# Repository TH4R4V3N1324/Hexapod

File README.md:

# Hexapod

This repository contains the complete design, control software and documentation for a six-legged walking robot (hexapod). The project combines robotics, kinematics, embedded systems, and motion planning to create a stable and adaptable walking platform.

---

## Table of Contents

- [About](#about)
- [Features](#features)
- [Installation](#installation)
  - [Hexapod](#hexapod)
  - [Receiver & Controller](#receiver--controller)
- [Usage](#usage)

---

## About

This project was developed to address the growing complexity in robotic control systems, where tightly coupled codebases often hinder scalability, debugging, and long-term maintainability. It is designed for developers, researchers, or engineers working with robotic platforms or automation systems who require a clean, extensible control framework that’s easy to understand and build upon.

The primary goal of the project was to emphasize modularity, ensuring that each component of the control software is clearly separated by function and responsibility. This modular design allows developers to quickly comprehend the structure of the system, make targeted changes without unintended side effects, and expand the system by adding new features or improving existing ones without rewriting the entire codebase.

To achieve this, the software is structured around a set of well-defined classes, each serving a distinct role:

- DataPacket Class: Acts as a container for incoming or outgoing data, ensuring that all communication between system components remains consistent, structured, and easily interpretable.

- Calculate Class: Handles all mathematical and logical computations required by the system, such as sensor data interpretation, decision-making algorithms, or movement planning.

- Move Class: Directly interfaces with the actuators or motors, translating high-level commands into specific movement instructions. It abstracts the hardware layer, allowing for easier adaptation across different platforms.

- Animation Class: Manages co-ordination of legs using the various gaits and modes to create walking and animation.

---

## Features

- 3 DOF per leg
- Inverse Kinematic engine for stable gait control
- Multiple gait patterns: tripod, ripple, wave
- Multiple control modes: normal, strafe, tilt
- Real-time control via Pimironi Servo2040
- Wireless control using custom controller and EspNOW protocol
- STL files for 3D-printing mechanical components

---

## Installation

Describe how to get your project running locally. Include prerequisites, dependencies, and step-by-step instructions.

Clone the repository into the desired location using the git bash terminal.
```bash
git clone https://github.com/TH4R4V3N1324/Hexapod.git
```

### Hexapod
Before getting started, make sure you have the following installed:

#### Prerequisites
- [Visual Studio Code](https://code.visualstudio.com/)
- [Pico SDK and cmake toolchain](https://github.com/raspberrypi/pico-sdk)
- [Raspberry Pi Pico VSCode Extension](https://marketplace.visualstudio.com/items?itemName=raspberry-pi.raspberry-pi-pico)

#### Dependencies
- [Pimironi pico sdk](https://github.com/pimoroni/pimoroni-pico.git)

Using the Raspberry Pi Pico VSCode extension, import the Hexapod sub-folder by selecting it in the **Location** tab, enabling **CMake-Tools** and clicking **Import**. 

A selection box will appear at the top of the screen. From the list, choose the appropriate Pico compiler.

Once imported, you can build the project by selecting **Compile Project** from the Pico extension commands. This will generate a .uf2 firmware file inside the build directory.

To flash the firmware to the Pimoroni Servo 2040, put the board into BOOTSEL mode (by holding the BOOT button and pressing RESET), then copy the .uf2 file to the mounted USB storage.

Alternatively, you can enter BOOTSEL mode first, then simply use the **Run Project** command. This will automatically build and flash the firmware to the board, no manual file transfer required.

### Receiver & Controller

#### Prerequisites
- [PlatformIO VSCode Extension](https://marketplace.visualstudio.com/items?itemName=platformio.platformio-ide)

#### Dependencies
- [u8g2 library](https://github.com/olikraus/u8g2.git)

Using the PlatformIO extension in VS Code, select the **Open** option under the **Quick Access** panel to launch the PlatformIO Home page. From there, click **Open Project** and navigate to the appropriate sub-folder to import your project.

To build or upload the project to your ESP32 board, use the **Build** or **Upload** options available under the **Project Tasks** panel in the PlatformIO extension.

---

## Usage

Explain how to use the project. Provide code snippets, screenshots, or examples as helpful.

# Ideas:
# Use ROS2 for control

## Package Structure

### 1. hexapod_description (URDF/Configuration)

- Robot URDF model with leg geometry
- Joint limits and physical parameters
- Launch files for simulation and hardware

### 2. hexapod_hardware_interface (Hardware Layer)

#### Servo Controller Node: Interfaces with PCA9685 or direct PWM

- Subscribes to: /joint_commands (JointState)
- Publishes: /joint_states (JointState with feedback)
- Service: /emergency_stop

#### Sensor Manager Node: Aggregates all sensor data

- Publishes: /imu/data (sensor_msgs/Imu)
- Publishes: /power/status (custom PowerStatus msg)
- Publishes: /leg_contact (custom LegContactArray msg)

### 3. hexapod_kinematics (Computation Layer)

#### IK/FK Solver Node: Your Calculate class logic
- Service: /ik_solve (Vector3 → JointAngles)
- Service: /fk_solve (JointAngles → Vector3)
- Subscribes to: /joint_states (JointState)
- Publishes: /leg_poses (geometry_msgs/PoseArray

### 4. hexapod_gait_controller (Motion Planning)

#### Gait Generator Node: Your Animation/Move logic

- Subscribes to: /cmd_vel (Twist for velocity commands)
- Subscribes to: /gait_mode (String: tripod/ripple/wave)
- Publishes: /leg_trajectories (trajectory_msgs/JointTrajectory)
- Action Server: /execute_gait for complex movements

### 5. hexapod_control (High-Level Control)

#### Behavior Manager Node: State machine (Normal/Strafe/Tilt/Config)

- Subscribes to: /mode_command (custom ModeCommand)
- Subscribes to: /joystick (sensor_msgs/Joy)
- Publishes: /cmd_vel (Twist)
- Service: /set_height, /home_stance

#### Config Manager Node: Servo offset calibration

- Reads/writes to parameter server
- Service: /save_config, /load_config

### 6. hexapod_teleop (User Interface)

#### Joystick Node: Replaces your ESP-NOW controller

- Uses joy_node from ROS2
- Publishes: /joystick (sensor_msgs/Joy)

#### Web Interface Node: Optional dashboard

- rqt plugins or custom web interface
- Monitor battery, IMU, leg contact

# Use Isaac sim for simulation

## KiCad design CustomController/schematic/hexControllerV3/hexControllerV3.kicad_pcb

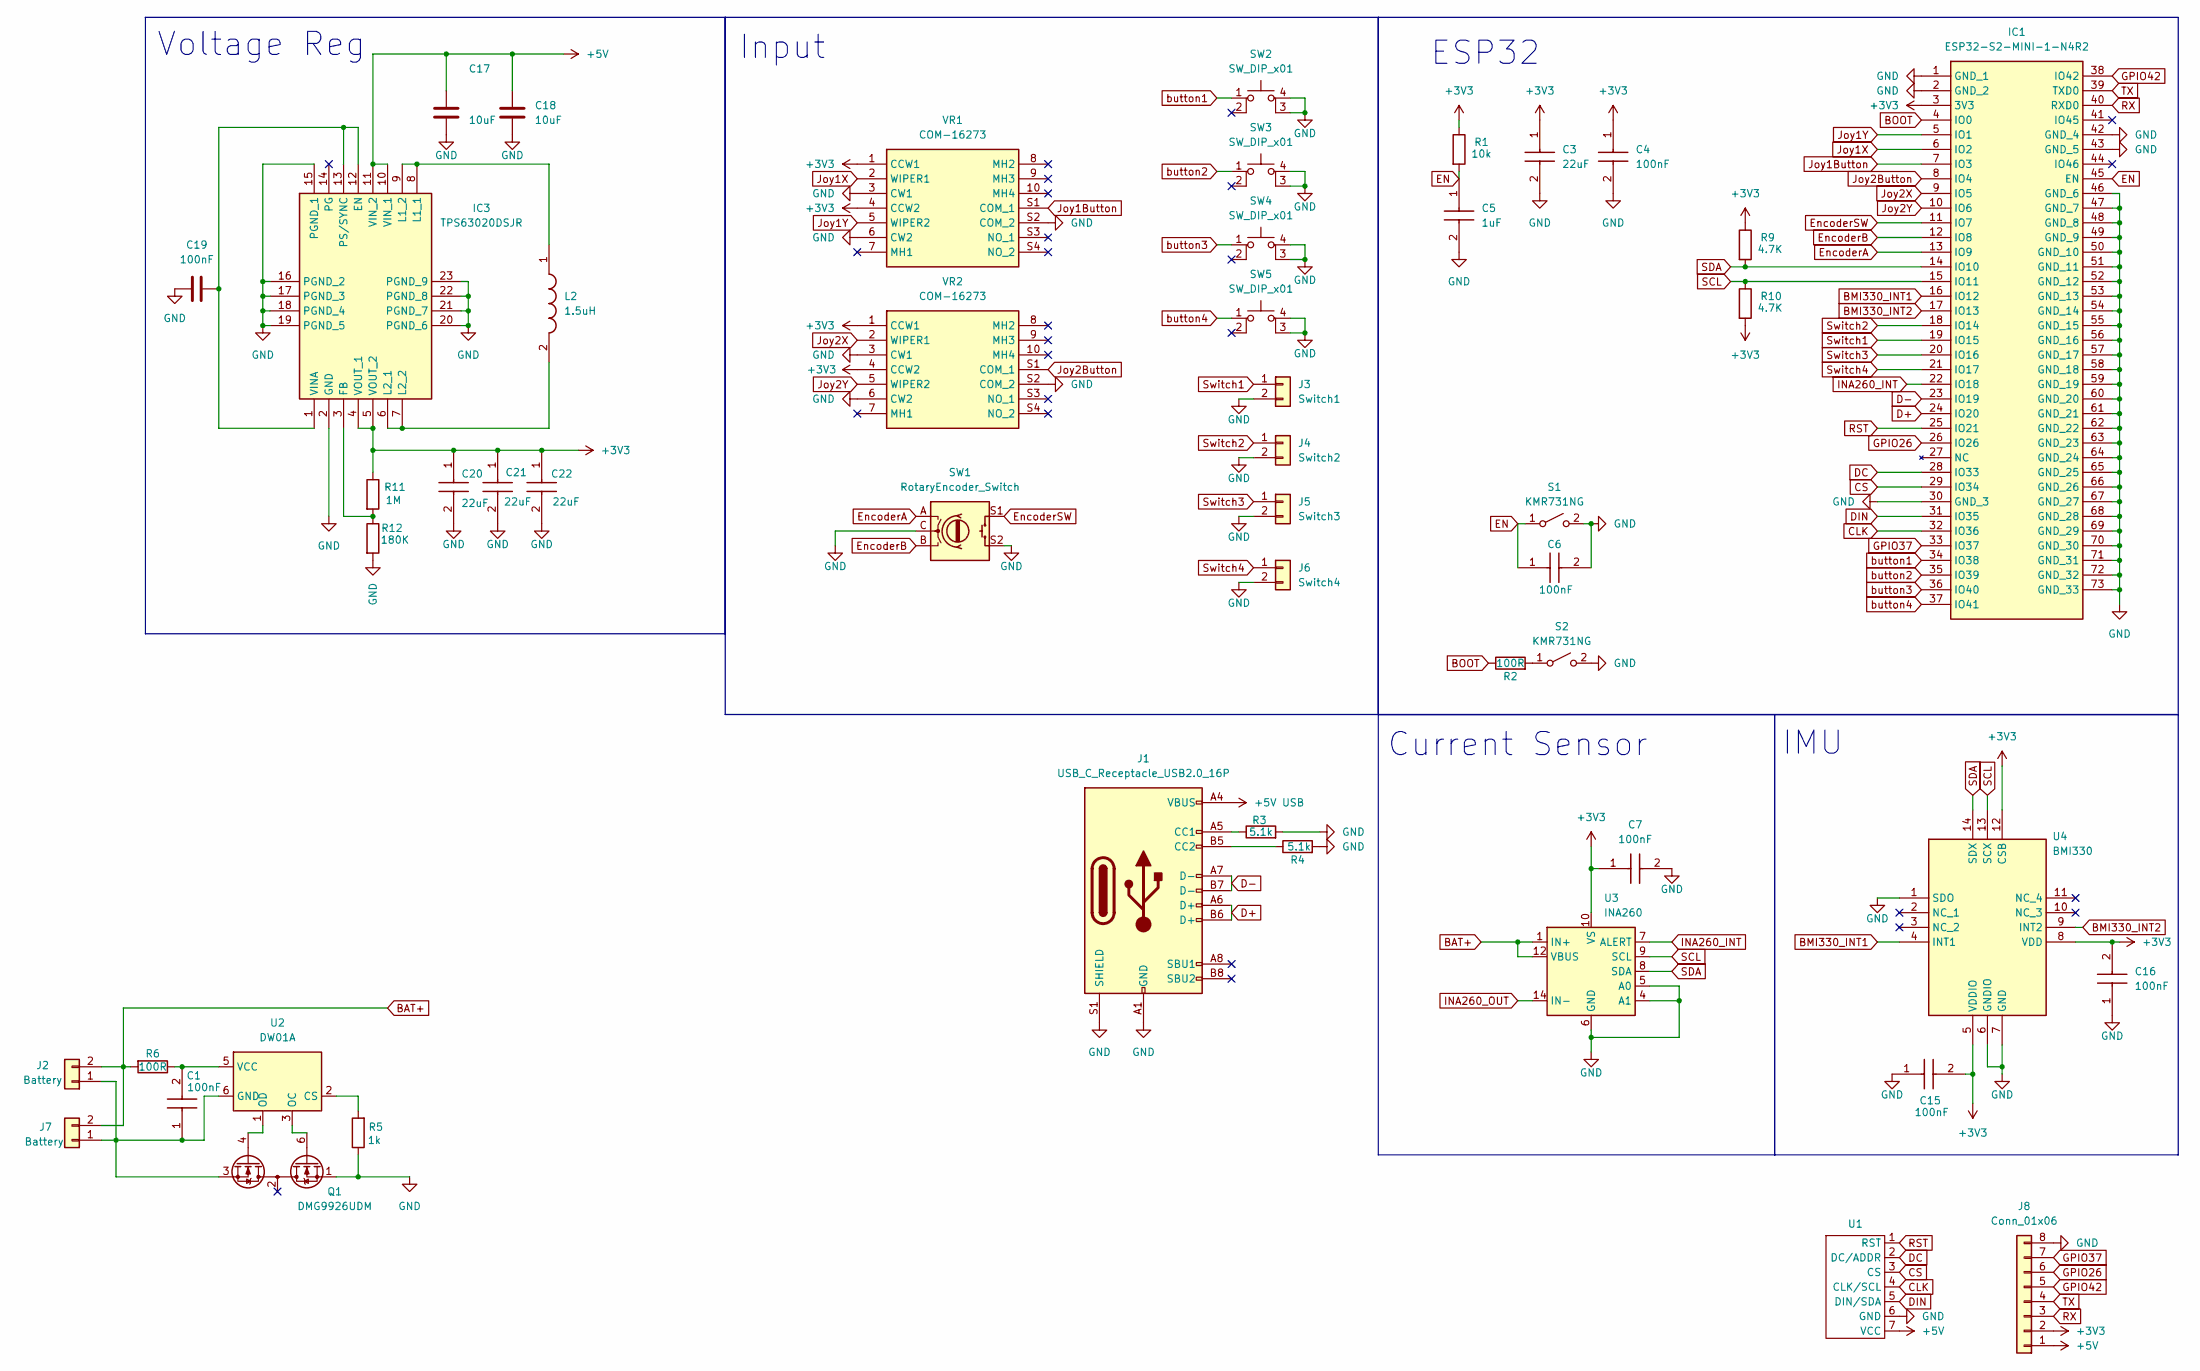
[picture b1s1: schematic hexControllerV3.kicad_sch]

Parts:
C1, C4, C6: 100nF; CAPC2012X95N; Manufacturer_Part_Number CC0805KRX7R9BB104; Mouser Part Number 603-CC805KRX7R9BB104
C3: 22uF; CAPC2012X140N; Manufacturer_Part_Number CL21A226MAQNNNE; Mouser Part Number 187-CL21A226MAQNNNE
C5: 1uF; CAPC2012X135N; Manufacturer_Part_Number CL21B105KBFNNNE; Mouser Part Number 187-CL21B105KBFNNNE
C7, C15, C16: 100nF; C_0805_2012Metric_Pad1.18x1.45mm_HandSolder; Manufacturer_Part_Number CC0805KRX7R9BB104; Mouser Part Number 603-CC805KRX7R9BB104
C17, C18: 10uF; C_0603_1608Metric_Pad1.08x0.95mm_HandSolder
C19: 100nF; C_0603_1608Metric_Pad1.08x0.95mm_HandSolder
C20, C21, C22: 22uF; C_0603_1608Metric_Pad1.08x0.95mm_HandSolder; Manufacturer_Part_Number CL21A226MAQNNNE; Mouser Part Number 187-CL21A226MAQNNNE
IC1: ESP32-S2-MINI-1-N4R2; ESP32S2MINI1N4R2; Manufacturer_Part_Number ESP32-S2-MINI-1-N4R2; Mouser Part Number 356-ESP32S2MINI1N4R2
IC3: TPS63020DSJR; Manufacturer_Part_Number TPS63020DSJR; Mouser Part Number 595-TPS63020DSJR
J1: USB_C_Receptacle_USB2.0_16P; USB_C_Receptacle_GCT_USB4105-xx-A_16P_TopMnt_Horizontal
J2, J7: Battery; PinHeader_1x02_P2.54mm_Vertical
J3: Switch1; PinHeader_1x02_P2.54mm_Vertical
J4: Switch2; PinHeader_1x02_P2.54mm_Vertical
J5: Switch3; PinHeader_1x02_P2.54mm_Vertical
J6: Switch4; PinHeader_1x02_P2.54mm_Vertical
J8: Conn_01x06; PinHeader_2x04_P2.54mm_Vertical
L2: 1.5uH; XAL40XX; Manufacturer_Part_Number XAL4020-102MEC; Mouser Part Number 994-XAL4020-102MEC
Q1: DMG9926UDM; SOT-23-6
R1: 10k; R_0805_2012Metric
R2, R6: 100R; R_0805_2012Metric
R3, R4: 5.1k; R_0805_2012Metric
R5: 1k; R_0805_2012Metric
R9, R10: 4.7K; R_0805_2012Metric
R11: 1M; R_0603_1608Metric
R12: 180K; R_0603_1608Metric
S1, S2: KMR731NG; SW_Push_1P1T_NO_CK_KMR2; Manufacturer_Part_Number TS-1088-AR02016
SW1: RotaryEncoder_Switch; PEC11L4120FS0020
SW2, SW3, SW4, SW5: SW_DIP_x01; DTS62NV
U1: WaveShare_2.42inch_SSD1309_OLED
U2: DW01A; SOT-23-6
U3: INA260; TSSOP-16_4.4x5mm_P0.65mm
U4: BMI330; Manufacturer_Part_Number BMI330
VR1, VR2: COM-16273; COM16273; Mouser Part Number 474-COM-16273

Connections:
+3V3: C3.1, C4.1, C7.1, C15.2, C16.2, C20.1, C21.1, C22.1, IC1.3 (3V3), IC3.4 (VOUT_1), IC3.5 (VOUT_2), J8.2, R1.1, R9.1, R10.2, R11.1, U3.10 (VS), U4.5 (VDDIO), U4.8 (VDD), U4.12 (CSB), VR1.1 (CCW1), VR1.4 (CCW2), VR2.1 (CCW1), VR2.4 (CCW2)
+5V: C17.1, C18.1, IC3.10 (VIN_1), IC3.11 (VIN_2), J8.1, U1.7 (VCC)
+5V USB: J1.A4 (VBUS), J1.A9 (VBUS), J1.B4 (VBUS), J1.B9 (VBUS)
BAT+: J2.2, J7.2, R6.2, U3.1 (IN+), U3.2 (IN+), U3.3 (IN+), U3.12 (VBUS)
BMI330_INT1: IC1.16 (IO12), U4.4 (INT1)
BMI330_INT2: IC1.17 (IO13), U4.9 (INT2)
BOOT: IC1.4 (IO0), R2.1
CLK: IC1.32 (IO36), U1.4 (CLK/SCL)
CS: IC1.29 (IO34), U1.3 (CS)
D+: IC1.24 (IO20), J1.A6 (D+), J1.B6 (D+)
D-: IC1.23 (IO19), J1.A7 (D-), J1.B7 (D-)
DC: IC1.28 (IO33), U1.2 (DC/ADDR)
DIN: IC1.31 (IO35), U1.5 (DIN/SDA)
EN: C5.1, C6.1, IC1.45 (EN), R1.2, S1.1 (A)
EncoderA: IC1.13 (IO9), SW1.A
EncoderB: IC1.12 (IO8), SW1.B
EncoderSW: IC1.11 (IO7), SW1.S1
GND: C3.2, C4.2, C5.2, C6.2, C7.2, C15.1, C16.1, C17.2, C18.2, C19.2, C20.2, C21.2, C22.2, IC1.1 (GND_1), IC1.2 (GND_2), IC1.30 (GND_3), IC1.42 (GND_4), IC1.43 (GND_5), IC1.46 (GND_6), IC1.47 (GND_7), IC1.48 (GND_8), IC1.49 (GND_9), IC1.50 (GND_10), IC1.51 (GND_11), IC1.52 (GND_12), IC1.53 (GND_13), IC1.54 (GND_14), IC1.55 (GND_15), IC1.56 (GND_16), IC1.57 (GND_17), IC1.58 (GND_18), IC1.59 (GND_19), IC1.60 (GND_20), IC1.61 (GND_21), IC1.62 (GND_22), IC1.63 (GND_23), IC1.64 (GND_24), IC1.65 (GND_25), IC1.66 (GND_26), IC1.67 (GND_27), IC1.68 (GND_28), IC1.69 (GND_29), IC1.70 (GND_30), IC1.71 (GND_31), IC1.72 (GND_32), IC1.73 (GND_33), IC3.2 (GND), IC3.15 (PGND_1), IC3.16 (PGND_2), IC3.17 (PGND_3), IC3.18 (PGND_4), IC3.19 (PGND_5), IC3.20 (PGND_6), IC3.21 (PGND_7), IC3.22 (PGND_8), IC3.23 (PGND_9), J1.A1 (GND), J1.A12 (GND), J1.B1 (GND), J1.B12 (GND), J1.S1 (SHIELD), J3.2, J4.2, J5.2, J6.2, J8.8, Q1.1 (D1), R3.2, R4.2, R5.1, R12.2, S1.2 (B), S2.2 (B), SW1.C, SW1.S2, SW2.3 (K), SW2.4 (A), SW3.3 (K), SW3.4 (A), SW4.3 (K), SW4.4 (A), SW5.3 (K), SW5.4 (A), U1.6 (GND), U3.4 (A1), U3.5 (A0), U3.6 (GND), U3.11 (GND), U4.1 (SDO), U4.6 (GNDIO), U4.7 (GND), VR1.3 (CW1), VR1.6 (CW2), VR1.S2 (COM_2), VR2.3 (CW1), VR2.6 (CW2), VR2.S2 (COM_2)
GPIO26: IC1.26 (IO26), J8.6
GPIO37: IC1.33 (IO37), J8.7
GPIO42: IC1.38 (IO42), J8.5
INA260_INT: IC1.22 (IO18), U3.7 (ALERT)
INA260_OUT: U3.14 (IN-), U3.15 (IN-), U3.16 (IN-)
Joy1Button: IC1.7 (IO3), VR1.S1 (COM_1)
Joy1X: IC1.6 (IO2), VR1.2 (WIPER1)
Joy1Y: IC1.5 (IO1), VR1.5 (WIPER2)
Joy2Button: IC1.8 (IO4), VR2.S1 (COM_1)
Joy2X: IC1.9 (IO5), VR2.2 (WIPER1)
Joy2Y: IC1.10 (IO6), VR2.5 (WIPER2)
unnamed: C19.1, IC3.1 (VINA), IC3.12 (EN), IC3.13 (PS/SYNC)
unnamed: IC3.3 (FB), R11.2, R12.1
unnamed: IC3.8 (L1_1), IC3.9 (L1_2), L2.1
unnamed: IC3.6 (L2_1), IC3.7 (L2_2), L2.2
unnamed: J1.A5 (CC1), R3.1
unnamed: J1.B5 (CC2), R4.1
unnamed: C1.1, J2.1, J7.1, Q1.3 (S2), U2.6 (GND)
unnamed: Q1.6 (G1), U2.3 (OC)
unnamed: Q1.4 (G2), U2.1 (OD)
unnamed: R2.2, S2.1 (A)
unnamed: R5.2, U2.2 (CS)
unnamed: C1.2, R6.1, U2.5 (VCC)
RST: IC1.25 (IO21), U1.1 (RST)
RX: IC1.40 (RXD0), J8.3
SCL: IC1.15 (IO11), R10.1, U3.9 (SCL), U4.13 (SCX)
SDA: IC1.14 (IO10), R9.2, U3.8 (SDA), U4.14 (SDX)
Switch1: IC1.19 (IO15), J3.1
Switch2: IC1.18 (IO14), J4.1
Switch3: IC1.20 (IO16), J5.1
Switch4: IC1.21 (IO17), J6.1
TX: IC1.39 (TXD0), J8.4
button1: IC1.34 (IO38), SW2.1
button2: IC1.35 (IO39), SW3.1
button3: IC1.36 (IO40), SW4.1
button4: IC1.37 (IO41), SW5.1

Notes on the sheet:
IMU
Current Sensor
Input
ESP32
Voltage Reg

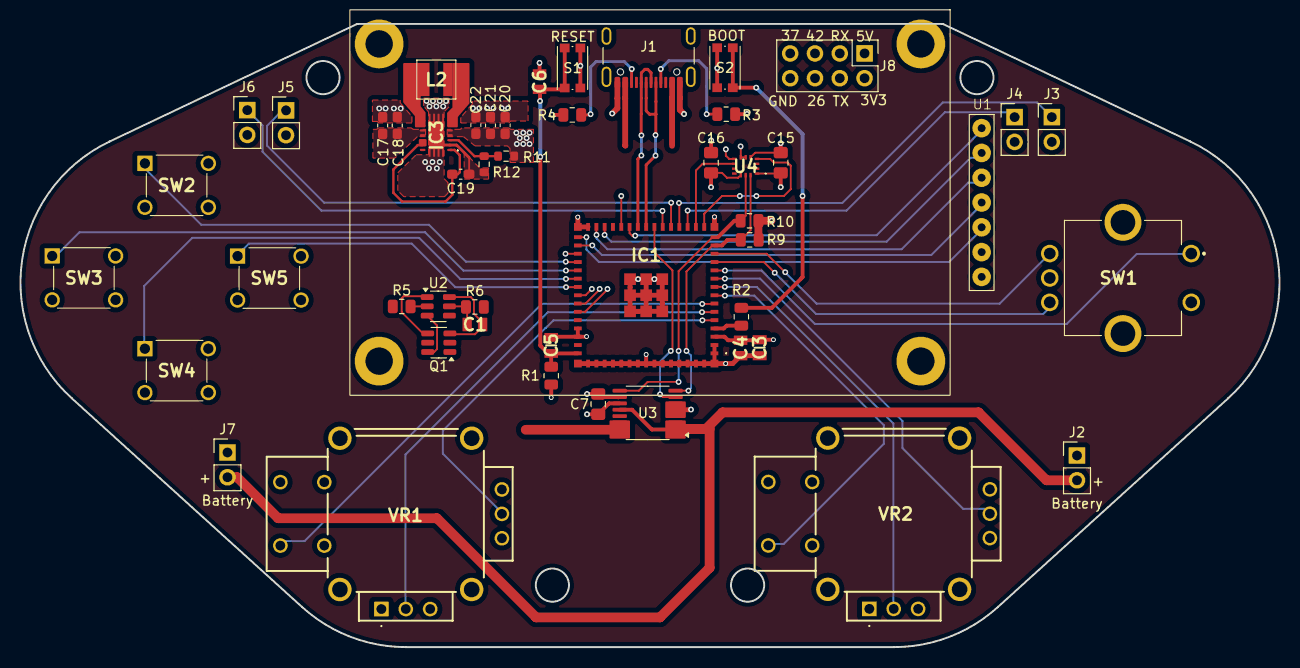
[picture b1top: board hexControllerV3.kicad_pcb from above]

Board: 4 copper layers, 129.0 x 63.9 mm, 49 parts (0 on the bottom side), 54 nets.

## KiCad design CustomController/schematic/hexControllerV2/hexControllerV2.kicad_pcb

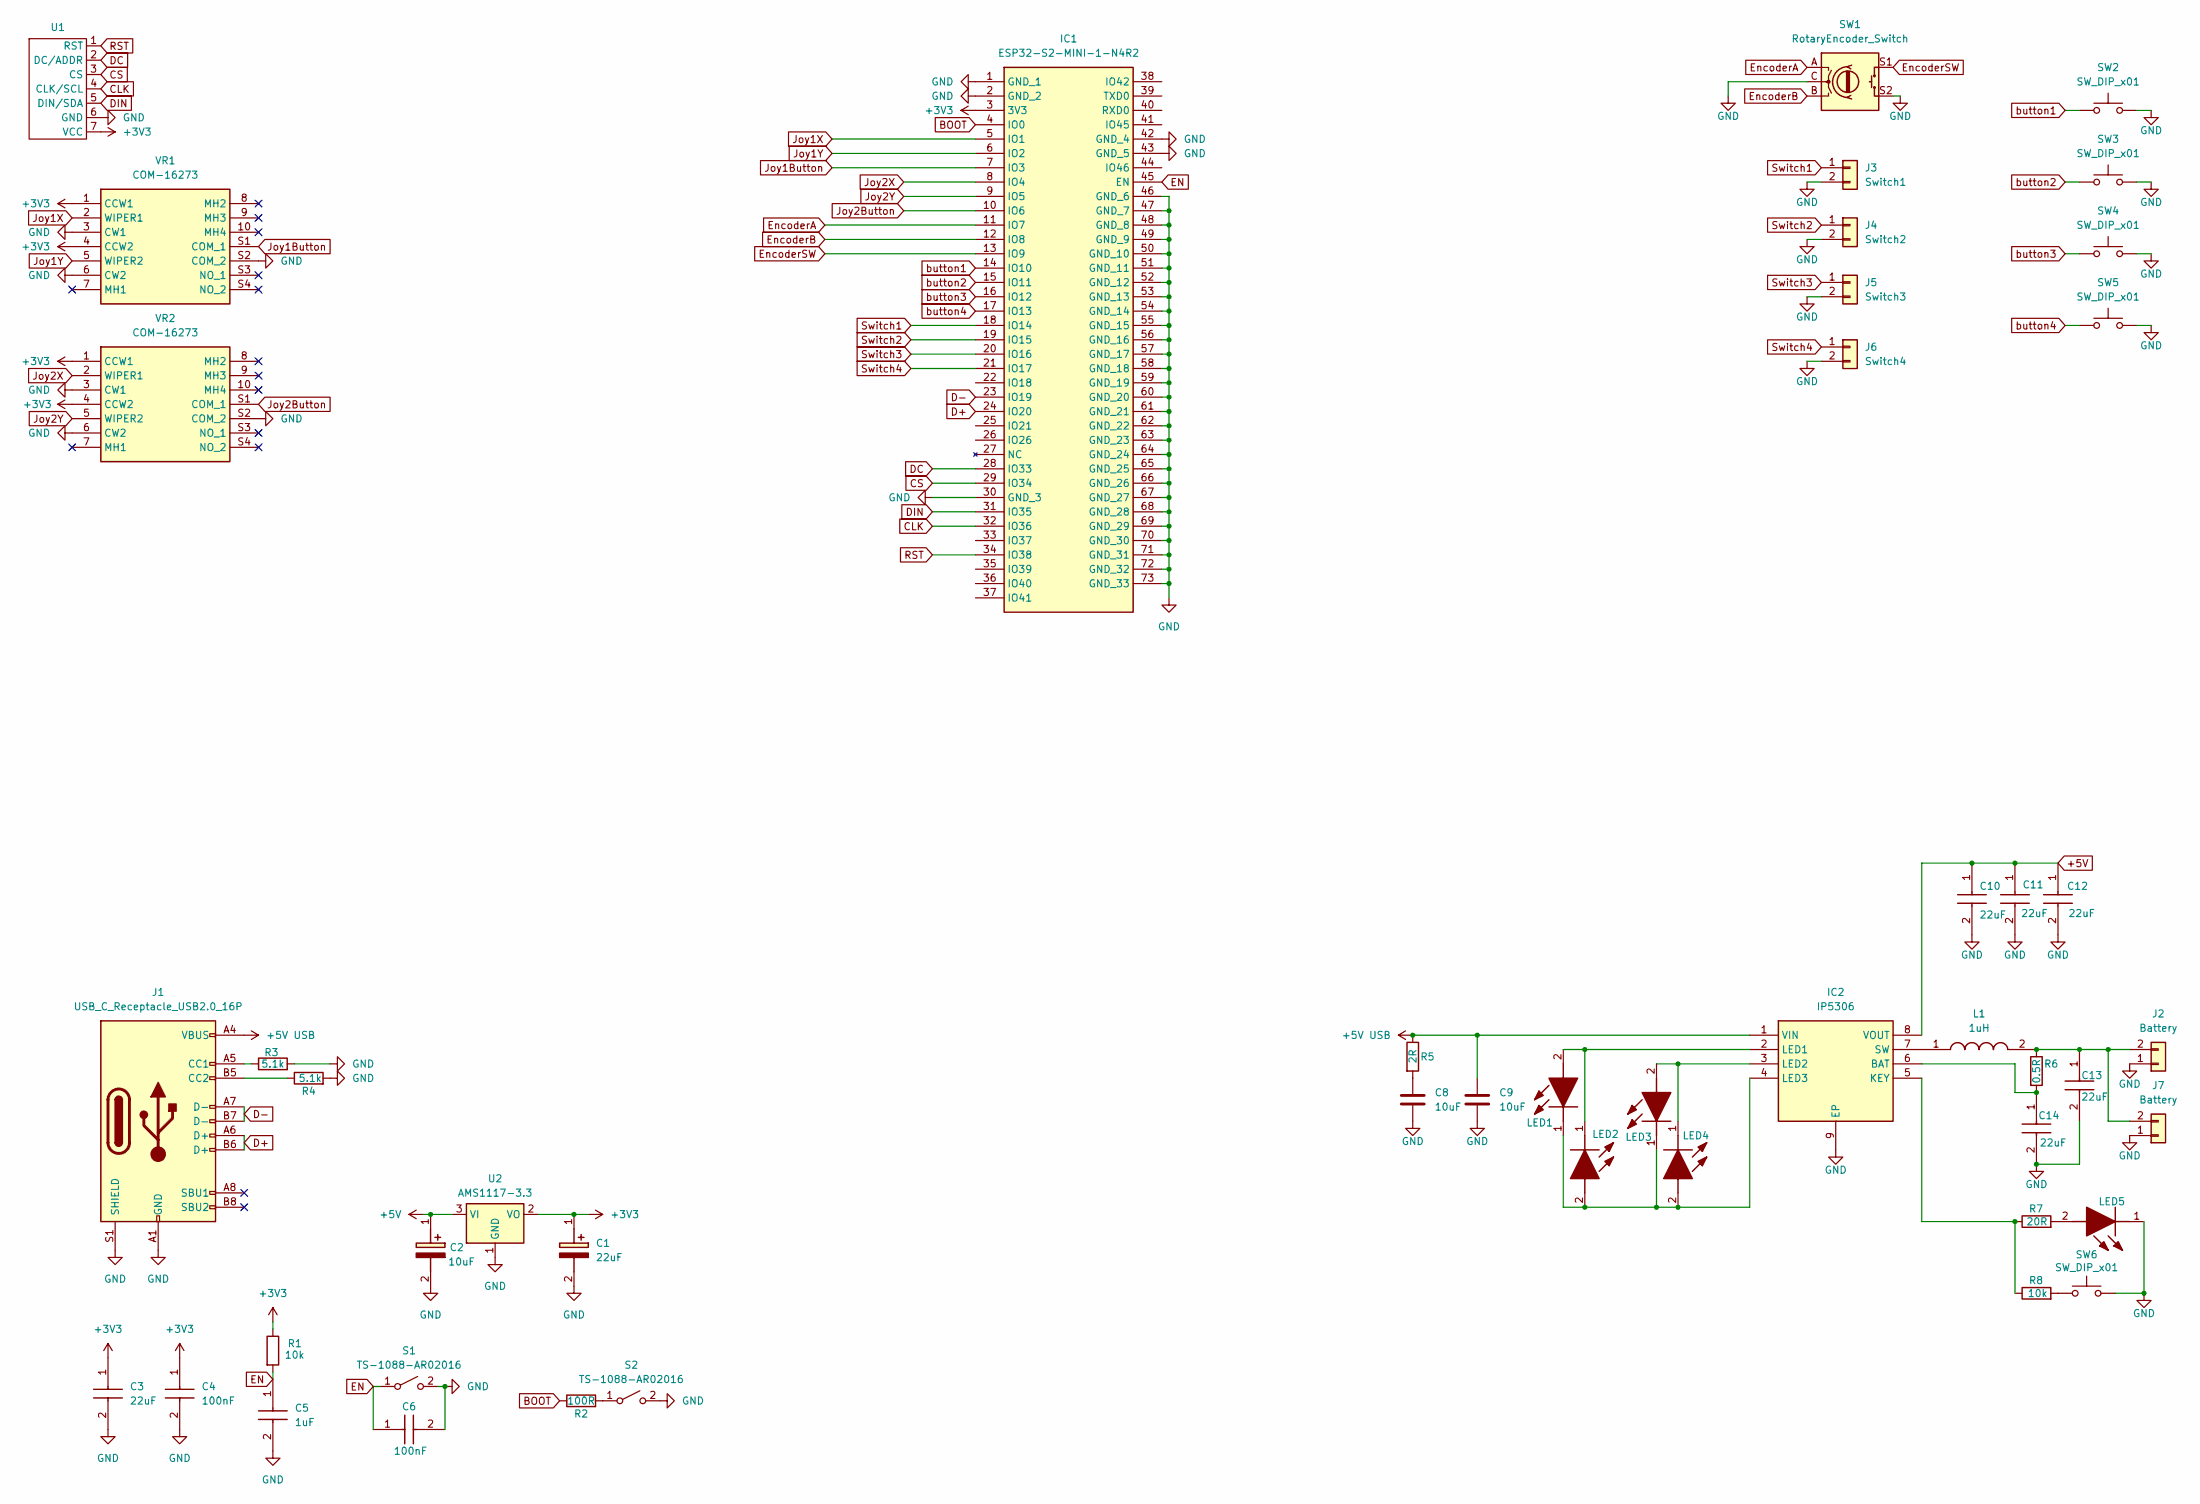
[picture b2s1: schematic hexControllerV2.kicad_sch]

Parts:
C1: 22uF; CAPPM3528X210N; Manufacturer_Part_Number TCJB226M025R0150E; Mouser Part Number 581-CJB226M025R0150E
C2: 10uF; CAPPM3216X180N; Manufacturer_Part_Number TAJA106K016RNJ; Mouser Part Number 581-TAJA106K016R
C3, C10, C11, C12, C13, C14: 22uF; CAPC2012X140N; Manufacturer_Part_Number CL21A226MAQNNNE; Mouser Part Number 187-CL21A226MAQNNNE
C4, C6: 100nF; CAPC2012X95N; Manufacturer_Part_Number CC0805KRX7R9BB104; Mouser Part Number 603-CC805KRX7R9BB104
C5: 1uF; CAPC2012X135N; Manufacturer_Part_Number CL21B105KBFNNNE; Mouser Part Number 187-CL21B105KBFNNNE
C8, C9: 10uF; C_0805_2012Metric
IC1: ESP32-S2-MINI-1-N4R2; ESP32S2MINI1N4R2; Manufacturer_Part_Number ESP32-S2-MINI-1-N4R2; Mouser Part Number 356-ESP32S2MINI1N4R2
IC2: IP5306; SOIC127P600X165-9N; Manufacturer_Part_Number IP5306
J1: USB_C_Receptacle_USB2.0_16P; USB_C_Receptacle_GCT_USB4105-xx-A_16P_TopMnt_Horizontal
J2, J7: Battery; PinHeader_1x02_P2.54mm_Vertical
J3: Switch1; PinHeader_1x02_P2.54mm_Vertical
J4: Switch2; PinHeader_1x02_P2.54mm_Vertical
J5: Switch3; PinHeader_1x02_P2.54mm_Vertical
J6: Switch4; PinHeader_1x02_P2.54mm_Vertical
L1: 1uH; XAL40XX; Manufacturer_Part_Number XAL4020-102MEC; Mouser Part Number 994-XAL4020-102MEC
LED1, LED2, LED3, LED4, LED5: KP1608SURCK; Manufacturer_Part_Number KP-1608SURCK; Mouser Part Number N/A
R1, R8: 10k; R_0805_2012Metric
R2: 100R; R_0805_2012Metric
R3, R4: 5.1k; R_0805_2012Metric
R5: 2R; R_0805_2012Metric
R6: 0.5R; R_0805_2012Metric
R7: 20R; R_0805_2012Metric
S1, S2: TS-1088-AR02016; TS1088AR02016; Manufacturer_Part_Number TS-1088-AR02016
SW1: RotaryEncoder_Switch; PEC11L4120FS0020
SW2, SW3, SW4, SW5, SW6: SW_DIP_x01; DTS62NV
U1: WaveShare_2.42inch_SSD1309_OLED
U2: AMS1117-3.3; SOT-223-3_TabPin2
VR1, VR2: COM-16273; COM16273; Mouser Part Number 474-COM-16273

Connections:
+3V3: C1.1 (+), C3.1, C4.1, IC1.3 (3V3), R1.1, U1.7 (VCC), U2.2 (VO), VR1.1 (CCW1), VR1.4 (CCW2), VR2.1 (CCW1), VR2.4 (CCW2)
+5V: C2.1 (+), C10.1, C11.1, C12.1, IC2.8 (VOUT), U2.3 (VI)
+5V USB: C9.1, IC2.1 (VIN), J1.A4 (VBUS), J1.A9 (VBUS), J1.B4 (VBUS), J1.B9 (VBUS), R5.1
BOOT: IC1.4 (IO0), R2.1
CLK: IC1.32 (IO36), U1.4 (CLK/SCL)
CS: IC1.29 (IO34), U1.3 (CS)
D+: IC1.24 (IO20), J1.A6 (D+), J1.B6 (D+)
D-: IC1.23 (IO19), J1.A7 (D-), J1.B7 (D-)
DC: IC1.28 (IO33), U1.2 (DC/ADDR)
DIN: IC1.31 (IO35), U1.5 (DIN/SDA)
EN: C5.1, C6.1, IC1.45 (EN), R1.2, S1.1 (A)
EncoderA: IC1.11 (IO7), SW1.A
EncoderB: IC1.12 (IO8), SW1.B
EncoderSW: IC1.13 (IO9), SW1.S1
GND: C1.2 (-), C2.2 (-), C3.2, C4.2, C5.2, C6.2, C8.2, C9.2, C10.2, C11.2, C12.2, C13.2, C14.2, IC1.1 (GND_1), IC1.2 (GND_2), IC1.30 (GND_3), IC1.42 (GND_4), IC1.43 (GND_5), IC1.46 (GND_6), IC1.47 (GND_7), IC1.48 (GND_8), IC1.49 (GND_9), IC1.50 (GND_10), IC1.51 (GND_11), IC1.52 (GND_12), IC1.53 (GND_13), IC1.54 (GND_14), IC1.55 (GND_15), IC1.56 (GND_16), IC1.57 (GND_17), IC1.58 (GND_18), IC1.59 (GND_19), IC1.60 (GND_20), IC1.61 (GND_21), IC1.62 (GND_22), IC1.63 (GND_23), IC1.64 (GND_24), IC1.65 (GND_25), IC1.66 (GND_26), IC1.67 (GND_27), IC1.68 (GND_28), IC1.69 (GND_29), IC1.70 (GND_30), IC1.71 (GND_31), IC1.72 (GND_32), IC1.73 (GND_33), IC2.9 (EP), J1.A1 (GND), J1.A12 (GND), J1.B1 (GND), J1.B12 (GND), J1.S1 (SHIELD), J2.1, J3.2, J4.2, J5.2, J6.2, J7.1, LED5.1 (K), R3.2, R4.2, S1.2 (B), S2.2 (B), SW1.C, SW1.S2, SW2.2, SW3.2, SW4.2, SW5.2, SW6.2, U1.6 (GND), U2.1 (GND), VR1.3 (CW1), VR1.6 (CW2), VR1.S2 (COM_2), VR2.3 (CW1), VR2.6 (CW2), VR2.S2 (COM_2)
Joy1Button: IC1.7 (IO3), VR1.S1 (COM_1)
Joy1X: IC1.5 (IO1), VR1.2 (WIPER1)
Joy1Y: IC1.6 (IO2), VR1.5 (WIPER2)
Joy2Button: IC1.10 (IO6), VR2.S1 (COM_1)
Joy2X: IC1.8 (IO4), VR2.2 (WIPER1)
Joy2Y: IC1.9 (IO5), VR2.5 (WIPER2)
unnamed: C8.1, R5.2
unnamed: C14.1, IC2.6 (BAT), R6.2
unnamed: IC2.5 (KEY), R7.1, R8.1
unnamed: IC2.2 (LED1), LED1.2 (A), LED2.1 (K)
unnamed: IC2.3 (LED2), LED3.2 (A), LED4.1 (K)
unnamed: IC2.4 (LED3), LED1.1 (K), LED2.2 (A), LED3.1 (K), LED4.2 (A)
unnamed: IC2.7 (SW), L1.1
unnamed: J1.A5 (CC1), R3.1
unnamed: J1.B5 (CC2), R4.1
unnamed: C13.1, J2.2, J7.2, L1.2, R6.1
unnamed: LED5.2 (A), R7.2
unnamed: R8.2, SW6.1
unnamed: R2.2, S2.1 (A)
RST: IC1.34 (IO38), U1.1 (RST)
Switch1: IC1.18 (IO14), J3.1
Switch2: IC1.19 (IO15), J4.1
Switch3: IC1.20 (IO16), J5.1
Switch4: IC1.21 (IO17), J6.1
button1: IC1.14 (IO10), SW2.1
button2: IC1.15 (IO11), SW3.1
button3: IC1.16 (IO12), SW4.1
button4: IC1.17 (IO13), SW5.1

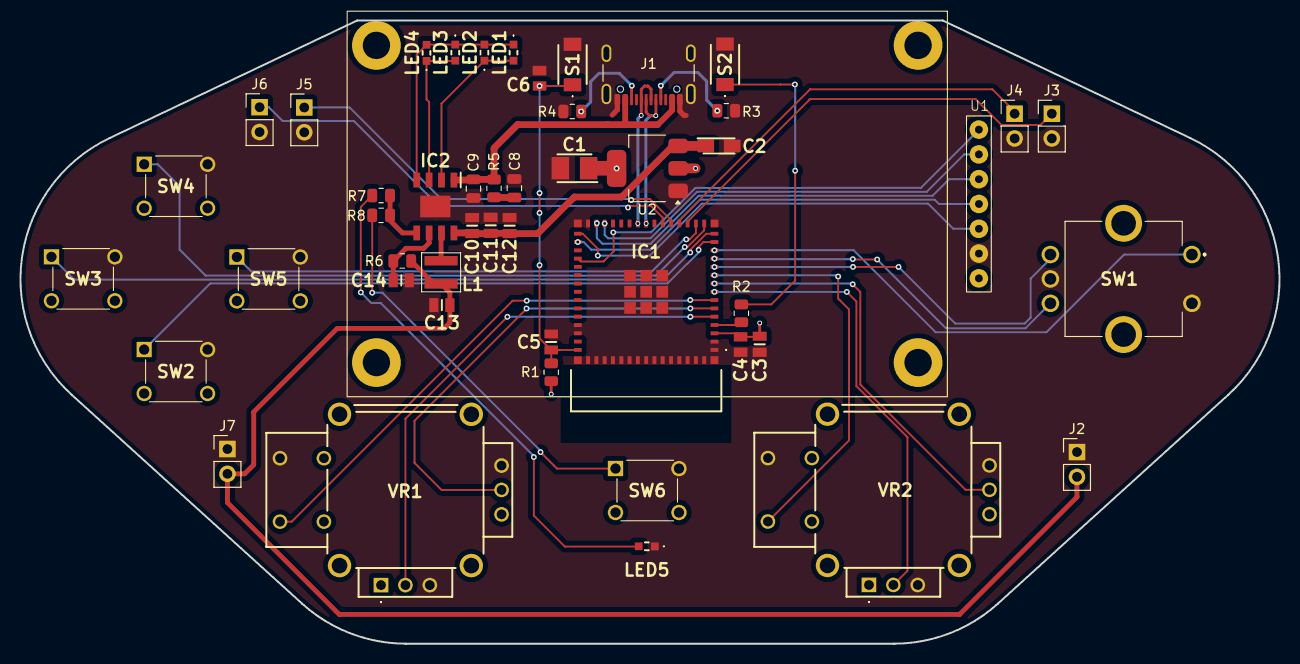
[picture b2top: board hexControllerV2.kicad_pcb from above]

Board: 4 copper layers, 129.0 x 63.9 mm, 48 parts (0 on the bottom side), 43 nets.

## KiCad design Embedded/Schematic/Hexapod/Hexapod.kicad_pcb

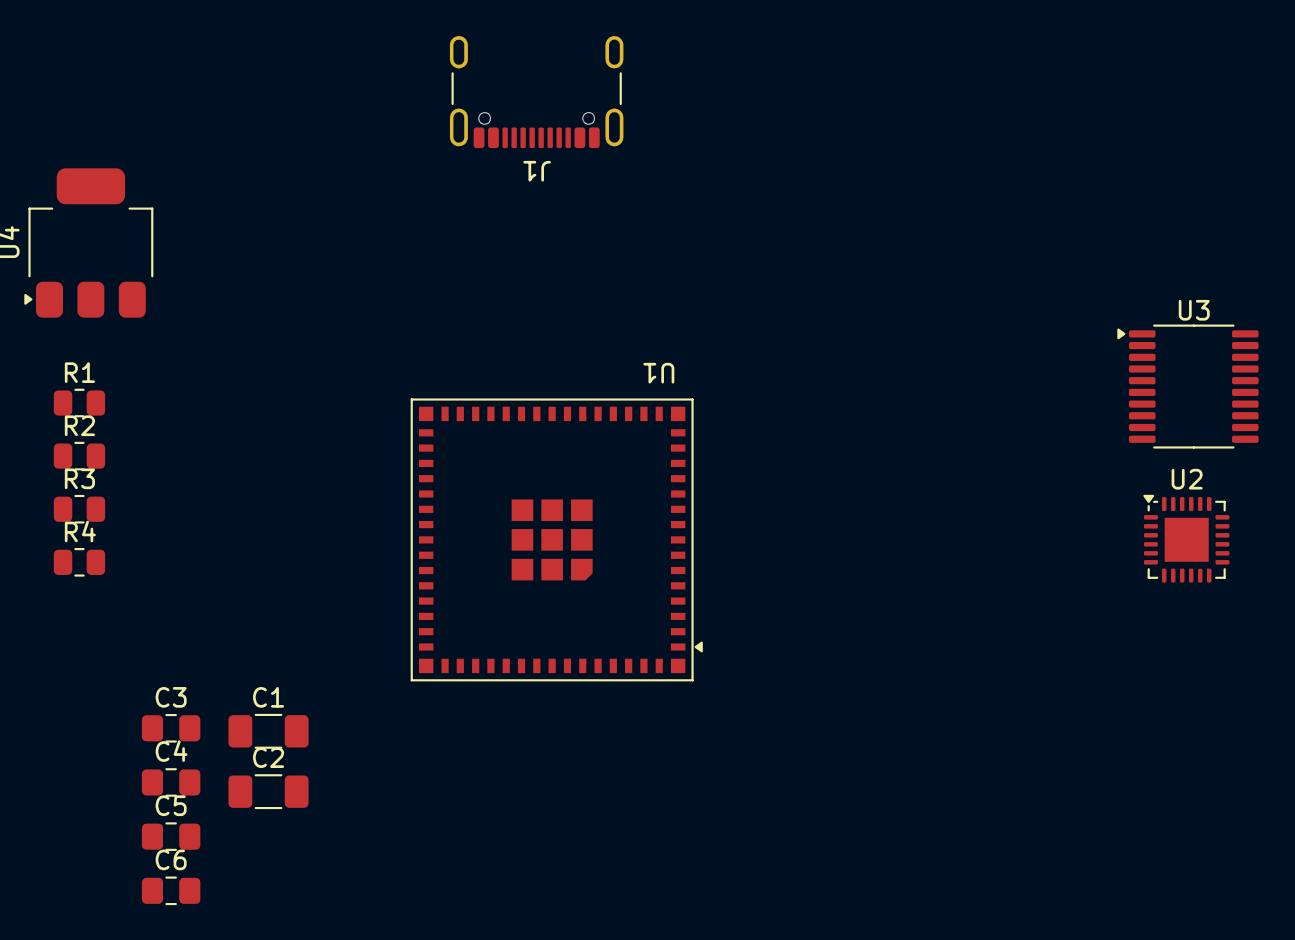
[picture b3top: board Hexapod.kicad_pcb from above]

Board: 2 copper layers, 15 parts (0 on the bottom side), 10 nets, no tracks yet.

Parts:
C1: 22uF; C_1206_3216Metric_Pad1.33x1.80mm_HandSolder
C2: 10uF; C_1206_3216Metric_Pad1.33x1.80mm_HandSolder
C3: 22uF; C_0805_2012Metric_Pad1.18x1.45mm_HandSolder
C4, C6: 100nF; C_0805_2012Metric_Pad1.18x1.45mm_HandSolder
C5: 1uF; C_0805_2012Metric_Pad1.18x1.45mm_HandSolder
J1: USB_C_Receptacle_USB2.0_16P; USB_C_Receptacle_GCT_USB4105-xx-A_16P_TopMnt_Horizontal
R1: 10k; R_0805_2012Metric
R2: 100R; R_0805_2012Metric
R3, R4: 5.1k; R_0805_2012Metric
U1: ESP32-S3-MINI-1U; ESP32-S2-MINI-1U
U2: BQ24610; VQFN-24-1EP_4x4mm_P0.5mm_EP2.45x2.45mm
U3: BQ76920PW; TSSOP-20_4.4x6.5mm_P0.65mm
U4: AMS1117-3.3; SOT-223-3_TabPin2

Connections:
+3V3: C1.1 (+), C3.1, C4.1, R1.1, U1.3 (3V3), U2.24 (VCC), U3.9 (REGSRC), U4.2 (VO)
+5V: C2.1 (+), U4.3 (VI)
+5V USB: J1.A4 (VBUS), J1.A9 (VBUS), J1.B4 (VBUS), J1.B9 (VBUS)
BOOT: R2.1, U1.4 (IO0)
D+: J1.A6 (D+), J1.B6 (D+), U1.24 (USB_D+)
D-: J1.A7 (D-), J1.B7 (D-), U1.23 (USB_D-)
EN: C5.1, C6.1, R1.2, U1.45 (EN)
GND: C1.2 (-), C2.2 (-), C3.2, C4.2, C5.2, C6.2, J1.A1 (GND), J1.A12 (GND), J1.B1 (GND), J1.B12 (GND), J1.S1 (SHIELD), R3.2, R4.2, U1.1 (GND), U1.2 (GND), U1.42 (GND), U1.43 (GND), U1.46 (GND), U1.47 (GND), U1.48 (GND), U1.49 (GND), U1.50 (GND), U1.51 (GND), U1.52 (GND), U1.53 (GND), U1.54 (GND), U1.55 (GND), U1.56 (GND), U1.57 (GND), U1.58 (GND), U1.59 (GND), U1.60 (GND), U1.61 (GND), U1.62 (GND), U1.63 (GND), U1.64 (GND), U1.65 (GND), U2.17 (GND), U2.25 (GND), U3.3 (VSS), U4.1 (GND)
unnamed: J1.A5 (CC1), R3.1
unnamed: J1.B5 (CC2), R4.1

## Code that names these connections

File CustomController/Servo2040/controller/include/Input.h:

#ifndef INPUT_H
#define INPUT_H
#include "DataPacket.h"
#include <stdint.h>
#include <Arduino.h>
#define stick1X 2
#define stick1Y 1
#define stick2X 5 
#define stick2Y 6 
#define button1 38
#define button2 39
#define button3 40
#define button4 41
#define switch1 15
#define switch2 14
#define switch3 16
#define switch4 17
#define encoderA 9
#define encoderB 8
#define encoderButton 7

// Declaration of encoder states
enum EncoderStates {AB, Ab, aB, ab};

class Input {
private:
    static EncoderStates encoderState;
    int center1X = 0;
    int center1Y = 0;
    int center2X = 0;
    int center2Y = 0;

public:
    static volatile int encoderCount;
    int lastEncoderCount = 0;
    int encoderDelta = 0;
    int encoderCountPerIndent = 4;
    bool button1Z0 = false;
    bool button1Z1 = false;
    bool button2Z0 = false;
    bool button2Z1 = false;
    bool button3Z0 = false;
    bool button3Z1 = false;
    bool button4Z0 = false;
    bool button4Z1 = false;
    bool encoderButtonZ0 = false;
    bool encoderButtonZ1 = false;
    void readStickData();
    void readButtonData();
    void readInputData();
    static void doEncoderFSM();
    void initializeEncoder();
    void initializeInput();
    int calibrateCenter(int pin);
    void initializeJoystick();
};

extern Input input;

#endif

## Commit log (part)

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2025-07-19 Moved command and command arguments to DataPacket.cpp
2025-07-19 Added methods to set gait and mode in Animation class
2025-07-19 Added ConfigManager Class for managing leg offsets in Hexapod project
2025-07-19 Added functionality to command and mode FSMs
2025-07-19 Added call to load leg offsets in main initialization
2025-07-20 Removed padding from data structures
2025-07-20 Controller retreives current height from hexapod on startup
2025-07-21 Reworked controller code using PlatformIO
2025-07-21 Correct logic errors in initialization and data handling
2025-07-22 Removed redundant files
2025-07-22 Added == operator to Vector3
2025-07-22 Added EnsureGaitConfig helper function to Animation class
2025-07-22 Added GenerateTrajectories helper Function to Animation class
2025-07-22 Simplified ReturnToStart Function using helper methods
2025-07-22 Fixed rotation logic in Normal mode
2025-07-23 Added method to convert positions to leg frame
2025-07-24 Added the forward kinematics function to Calculate class
2025-07-24 Moved jointOffset applictaion to seperate function in Calculate class
2025-07-24 Added type saftey to hexPacket gait and mode, Moved enums to DataPacket
2025-07-28 Added controller schematic
2025-07-29 Changed schematic/ PCB
2025-08-27 Changed pin config in code
2025-08-27 Added clamping to leg config in config state
2025-09-02 Initial commit of hexapod ESP32-S3 project files
2025-09-02 Reworked ConfigManager class for ESP32-S3 compatibility
2025-09-02 Added method of setting servo angle
2025-09-02 Added build flag -std=c++17
2025-09-02 Refactor servo angle setting methods in Move class for consistency
2025-09-02 Add Hexapod class and implement command/state finite state machines
2025-09-02 Add comments for clarity in DataPacket, Servo, and main files
2025-09-02 Reverted back to Controller managing data timing
2025-09-03 Add Sensor class definition with LegContactSensor initialization
2025-09-03 Refactor LegContactSensor to use static const LEG_SENSORS array for GPIO pin management
2025-09-03 Implement CurrentSensor methods and update initialization
2025-09-03 Update ESP32-S3 BOM spreadsheet for component tracking
2025-09-03 Initialize I2CManager in setup function for I2C communication
2025-09-03 Expose getPitch() and getRoll() methods in IMUSensor class
2025-09-03 Add comment to clarify updateOrientation method functionality
2025-09-03 Update BOM file for Hexapod project
2025-09-05 Refactor LegContactSensor::init method for improved clarity and structure
2025-09-05 Implement read and write register methods in I2CManager for enhanced I2C communication
2025-09-05 Add return value documentation for I2CManager read/write methods
2025-09-05 Add detailed documentation for Calculate class methods to improve code clarity
2025-09-05 Add detailed documentation for Servo class methods to improve code clarity
2025-09-05 Add detailed documentation for CurrentSensor methods to improve code clarity
2025-09-05 Add detailed documentation for GetLegConfig method to improve code clarity
2025-09-05 Add detailed documentation for ESP-NOW initialization and command change detection functions to improve code clarity
2025-09-05 Add detailed documentation for ControllerLogic, DataPacket, Display, Input, and Pages methods to improve code clarity
2025-09-05 Changed IMU config setup
2025-09-12 Editted schematic
2025-09-16 Changed schematic
2025-12-13 Initial commit controllerV2 board template
2025-12-13 Refactor code structure for improved readability and maintainability
2025-12-14 Remove inclusion of normal_mode_icon.c from main.c
2025-12-14 Refactor menuPage to dynamically set dropdown options for Gait and Mode
2025-12-14 Update menuPage to use display resolution for menu size and add Apply button
2025-12-15 Refactor menu structure to include destination page pointers in menu items for improved navigation and code clarity
2025-12-15 Initialize default theme in homePage and simplify menuPage styling
2025-12-15 Add debug page with SD card, flash size, battery voltage, board angle, RTC time, and wireless scan information
2025-12-16 Enhance home page layout by adding battery status display and improving styling for status bar
2025-12-16 Add uptime display to status bar on home page
2025-12-16 Add menu, gait, and mode buttons to home page action bar
2025-12-16 Implement battery voltage averaging and update display in homeInfo function
2025-12-16 Reorganised file structure
2025-12-17 Fixed LVGL linking issue
2025-12-17 Add leg animation functionality and structure definition
2025-12-17 Add hexapod eye and pupil rendering with reflections
2025-12-18 Fixed bug where screen wouldnt display anything on cold startup
2025-12-19 Increase battery averaging buffer size and adjust voltage percentage calculation for improved accuracy
2025-12-25 Update .gitignore to exclude additional build artifacts
2025-12-25 Add receiver connection status handling and update display connectivity indicator
2026-01-14 Initial commit Left Board
2026-01-14 Refactor debug page layout to use a helper function for creating input rows
2026-01-15 Uncomment left controller request and loop in app_main function
2026-01-15 Refactor UART controller request and receive logic for improved packet handling and timeout management
2026-01-15 Enhance uart_receive_loop to log checksum errors with details and assign joystick values to controlPacket based on request_cmd
2026-01-20 Update .gitignore to exclude all Visual Studio Code files
2026-01-23 organised file structure
2026-01-23 Fix leg positioning and orientation for rear and front right legs in hexapod URDF
2026-01-23 Initialize hexapod_kinematics package with CMakeLists.txt, package.xml, and .gitignore
2026-01-23 Initialize hexapod_control package with CMakeLists.txt, package.xml, and .gitignore
2026-01-23 Add kinematic_solver source file
2026-01-24 Add hexapod_interfaces package with CMakeLists.txt, package.xml, and .gitignore
2026-01-24 Add message definitions for LegContact and PowerStatus in hexapod_interfaces package
2026-01-24 Implement sensor data publishing in SensorManager class
2026-01-24 Add controller_bridge node for publishing controller_raw_data
2026-01-24 Add subscription information for joint states
2026-01-25 Enhance KinematicSolver: add joint state subscription and foot pose publishing, refactor FK request handling
2026-01-26 Refactor KinematicSolver constructor: inline service creation for IK and FK solvers
2026-01-26 Update ControllerInput message to ControllerRaw: unify input sources and enhance command structure
2026-01-26 Refactor ControllerBridge to use ControllerInput message and add ControllerInput message definition
2026-01-26 Refactor EspBridge to add IMU, PowerStatus, and LegContact publishers; implement emergency stop service
2026-01-27 Update CMakeLists and launch file: adjust installation paths for hardware_handlers and rename executable in launch configuration
2026-01-27 Update .gitignore and add c_cpp_properties for VSCode configuration
2026-01-27 Add FrameConverter class for leg and body frame transformations; update GaitController to include Eigen
2026-01-28 Update URDF file for hexapod: replace gazebo-specific model with simplified box geometry and add inertial properties; remove obsolete gazebo.urdf.xacro file.
2026-01-30 Refactor Gazebo launch file: replace ExecuteProcess with IncludeLaunchDescription for improved robot spawning and update URDF processing
2026-01-31 Enhance documentation for inverse and forward kinematics methods in KinematicSolver
2026-01-31 Refactor GaitController: add Mode enum and implement cycleMode and setMode methods for mode management
2026-01-31 Enhance GaitController and TrajectoryGenerator: add MAX_RESOLUTION constant, implement GaitState struct, and introduce CalculateStrideMultiplier and EnsureGaitConfig methods for improved gait managem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
2026-02-01 Enhance trajectory generation: add geometry_msgs dependency, implement direction calculation for joystick input, and introduce max_velocity and max_stride_length in GaitConfig for improved movement c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
2026-02-01 Add trajectory_generator library and update gait_controller for cmd_vel handling
    - Introduced trajectory_generator library with necessary source files.
    - Updated gait_controller to subscribe to cmd_vel and publish joint states.
    - Refactored kinematic_solver methods to follow camelCase naming convention.
    - Adjusted GenBezierTrajectory method signature in trajectory_generator.
2026-02-02 Implement HandleIdleReturn method for improved idle detection and return-to-start logic
2026-02-02 Refactor Normal method for car-like steering: remap lateral movement to angular.z and update documentation
2026-02-03 Refactor leg configuration and kinematics: update leg angles, improve IK/FK methods, and rename joint states for clarity
2026-02-03 Refactor frame conversion methods: implement rotation and translation for leg-to-body and body-to-leg transformations; update ExecuteGait liftHeight parameter to use meters; adjust trajectory collisi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
2026-02-03 Refactor GaitController: remove ExecuteGait method, integrate gait execution logic into Strafe and Normal methods, and enhance trajectory generation with improved leg position handling.
2026-02-03 Refactor returnToStart method in GaitController: remove unnecessary trajectoryGenerated flag and simplify logic for leg position estimation and phase handling.
2026-02-03 Refactor PerformLegStep method in GaitController: replace hardcoded MAX_RESOLUTION-1 with dynamic resolution parameter for improved flexibility in phase transition handling.
2026-02-04 Refactor trajectory generation and gait control: introduce SwingSpline structure for improved spline management, enhance target position blending with neutral position references, and implement expon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
2026-02-04 Add SetGait and SetMode service definitions: implement service interfaces for gait and mode control in hexapod.
2026-02-04 Fix default height in GaitConfig: change currentHeight from 0.15 to -0.15 for correct initialization.
2026-02-06 Enhance BlendTargetPosition: add legNum and strideMultiplier parameters for improved target blending and control.
2026-02-06 Add SetHeight service for dynamic height adjustment in gait controller
2026-02-08 Add hexapod_bringup package with CMakeLists.txt, package.xml, and launch file
2026-02-08 Format control instructions output in keyboard teleop for better readability
2026-02-09 Refactor gait control methods: replace Strafe and Normal with walk for improved clarity and functionality
2026-02-09 Add SetMode and SetGait service clients to keyboard teleop for improved gait and mode selection
2026-03-03 Refactor Dockerfile and docker-compose files for improved build configuration and development setup
2026-03-03 Refactor Dockerfile and docker-compose to standardize INSTALL_DEV_TOOLS argument
2026-03-07 Add .gitignore to exclude build, install, and log directories
2026-03-07 Refactor Docker Compose configuration for operator service; remove environment and volumes sections
2026-03-08 Add getCapabilities service callback and integrate with ControllerTeleop for dynamic gait and mode retrieval
2026-03-08 Remove ControllerHandler implementation and its references from hardware_interface_fake
2026-03-16 Added meshes to robot URDF
2026-03-17 Converted meshes to .dae format and included foxglove bridge on robot side
2026-03-17 Update mesh scaling in URDF: change scale from 0.01 to 1 for body, coxa, femur, and tibia
2026-03-21 Refactor Dockerfile: remove foxglove-bridge installation and clone from GitHub instead
2026-03-23 Fix subnet scanning in launch script to target 192.168 networks
2026-04-25 Add launch arguments for front depth camera configuration and improve joint state relay QoS
2026-04-30 Add RViz2 node to simulation launch configuration for visualization
2026-05-03 Refactor GaitController by removing unused trajectory regeneration methods and adding genSwingSpline for improved spline generation
